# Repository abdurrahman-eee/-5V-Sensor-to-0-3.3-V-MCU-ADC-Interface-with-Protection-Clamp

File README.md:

# ±5 V Sensor to 3.3 V MCU ADC Interface (Passive, Protected)

## Overview
This project provides a **robust, passive analog front-end** for interfacing a **−5 V to +5 V single-ended sensor output** (e.g. eddy-current or gap sensor) with a **3.3 V microcontroller ADC** (such as STM32).

The circuit safely maps the sensor signal into the ADC input range while protecting the MCU against **over-voltage, under-voltage, transients, wiring faults, and ESD-like events**, without using active components (op-amps).

---

## Key Features
- **Input Range:** −5 V to +5 V (single-ended, referenced to GND)
- **Output Range:** Safe for 0–3.3 V MCU ADC input
- **Passive Design:** Resistors, Schottky diodes, capacitor only
- **Over-/Under-Voltage Protection:** External Schottky clamp diodes
- **Current Limiting:** Series resistor to protect MCU pins
- **Fast Response:** Microsecond-scale electrical response
- **Noise Reduction:** Optional RC filtering without ms-level delay
- **Fail-Safe:** Protects MCU even during abnormal conditions

---

## Typical Use Cases
- Eddy-current displacement / gap sensors (±5 V output)
- Industrial or automotive test benches
- Engagement / disengagement detection systems
- Safety-critical ADC measurements
- MCU protection during sensor faults or miswiring

---

## Circuit Description

### 1. Voltage Mapping
A resistor network creates a **DC offset and scaling**, converting the ±5 V sensor signal into a mid-range voltage suitable for a 3.3 V ADC.

Normal operation keeps the ADC pin well within the valid input range, so the protection diodes remain **inactive**.

### 2. Protection Strategy
- **Series Resistor (R4):**
  - Limits current into the ADC pin and clamp diodes
  - Prevents excessive injection current during faults
- **Schottky Clamp Diodes:**
  - Upper clamp: limits ADC pin to ~3.3 V + Vf (~3.6 V)
  - Lower clamp: limits ADC pin to ~−0.3 V
  - External clamps conduct before internal MCU diodes
- **Optional Capacitor (C1):**
  - Filters high-frequency noise
  - Does not affect ms-level response

### 3. Fault Behavior
During abnormal input conditions (e.g. > ±5 V, ESD, cable issues):
- Voltage is clamped safely
- Current is limited to a few mA
- MCU pin remains within absolute maximum ratings

---

## Electrical Characteristics (Typical)

| Parameter | Value |
|---------|------|
| Sensor Input Range | −5 V to +5 V |
| ADC Safe Range | ~0.8 V to ~2.4 V (normal operation) |
| Clamp Voltage (High) | ~3.5–3.6 V |
| Clamp Voltage (Low) | ~−0.2 to −0.3 V |
| RC Time Constant | ~2–3 µs (with 2.2 kΩ + 1 nF) |
| Suitable ADC Sampling | 5–10 kHz (or higher) |

---

## Design Notes
- Grounds **must be common** between sensor and MCU
- Clamp diodes should be placed **close to the MCU ADC pin**
- Add local **0.1 µF decoupling** near the clamp connection to 3.3 V
- For harsh environments, a small series resistor to the clamp rail can be added
- This circuit prioritizes **robustness and safety** over precision amplification

---

## Limitations
- Passive scaling: not suitable if high accuracy or gain adjustment is required
- ADC reference noise directly affects measurement accuracy
- Not a differential input solution

For higher precision or isolation, consider an op-amp buffer or isolated ADC front-end.

---

## File Structure (Suggested)

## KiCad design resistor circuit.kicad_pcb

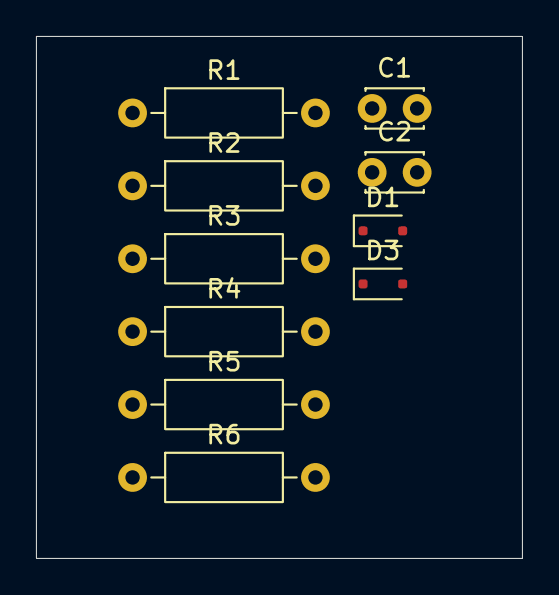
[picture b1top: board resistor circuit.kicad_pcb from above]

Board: 2 copper layers, 27.0 x 29.0 mm, 10 parts (0 on the bottom side), 6 nets, no tracks yet.

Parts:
C1: 1nF; C_Disc_D3.0mm_W2.0mm_P2.50mm
C2: 1u; C_Disc_D3.0mm_W2.0mm_P2.50mm
D1, D3: BAT54J; D_SOD-323F
R1: 10k; R_Axial_DIN0207_L6.3mm_D2.5mm_P10.16mm_Horizontal
R2: 3k3; R_Axial_DIN0207_L6.3mm_D2.5mm_P10.16mm_Horizontal
R3: 4k7; R_Axial_DIN0207_L6.3mm_D2.5mm_P10.16mm_Horizontal
R4: 2.2k; R_Axial_DIN0207_L6.3mm_D2.5mm_P10.16mm_Horizontal
R5, R6: 100; R_Axial_DIN0207_L6.3mm_D2.5mm_P10.16mm_Horizontal

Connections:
/Diode 3.3V: C2.1, D3.1 (K), R2.2
/Final Output: C1.2, R4.2, R5.1, R6.1
GND: C1.1, C2.2, D1.2 (A), R3.1
unnamed: D1.1 (K), R5.2
unnamed: D3.2 (A), R6.2
unnamed: R1.2, R2.1, R3.2, R4.1

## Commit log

2026-01-28 Initial commit: Resistor circuit design for -5V to 0-3.3V MCU ADC interface with protection clamp
2026-01-28 Add backups folder and .gitignore
2026-01-28 Add README with project details and specifications
    Added detailed project overview, key features, circuit description, electrical characteristics, design notes, and limitations for the sensor interface.
2026-01-28 add 100 ohm resistor
